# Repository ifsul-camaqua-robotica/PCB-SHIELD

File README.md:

# PCB-SHIELD
# Repositório para guardar o arquivo da PCB de um SHIELD para o carro da ROBOCUP 2025

- Arquivo "robocup-esp-32-1" -> Guarda os arquivos do KICAD para a PCB

- Arquivo "KICAD-LIBRARIES" -> Guarda as bibliotecas (footprints e symbols) utilizados para fazer a PCB
  (Não foi possível adicionar o arquivo da biblioteca utilizada "Espressif", porém no qual pode ser encontrada facilmente em repositório no github)

- Medindo do centro dos círculos até o centro deles.
- Cada um deles tem 3,5 mm das bordas (esta medida foi feita da borda dos círculos), e 3mm de diâmetro.
- Esquerda até Direita -> 84,5 mm
- Baixo até Cima -> 53mm

- Versão E-1.5

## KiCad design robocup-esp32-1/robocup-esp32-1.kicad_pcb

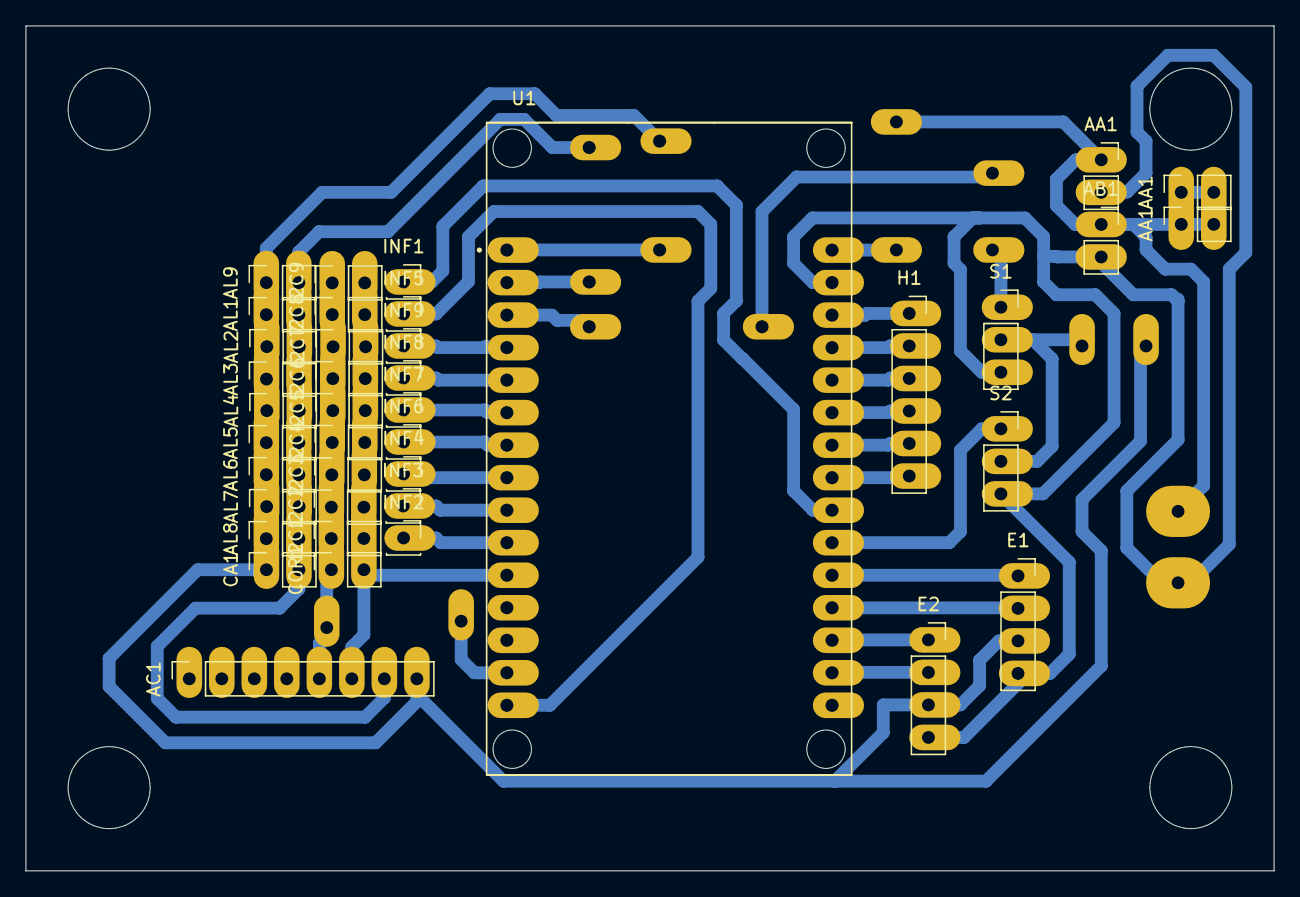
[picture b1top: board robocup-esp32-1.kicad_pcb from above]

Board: 2 copper layers, 97.5 x 66.0 mm, 40 parts (0 on the bottom side), 26 nets.

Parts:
AA1, AA1#2, AA1#3: VCCA, GNDA; PinSocket_1x02_P2.54mm_Vertical
AB1: VCCB, GNB; PinSocket_1x02_P2.54mm_Vertical
AC1: INT, ADD, XCL, XDA, SDA, SCL, GND, VCC; PinSocket_1x08_P2.54mm_Vertical
AL1, AL2, AL3, AL4, AL5, AL6, AL7, AL8, AL9: VCC, GND; PinSocket_1x02_P2.54mm_Vertical
CA1: VCC, GND; PinSocket_1x02_P2.54mm_Vertical
COR1: SDA, SCL; PinSocket_1x02_P2.54mm_Vertical
E1, E2: SA, SB, VCC, GND; PinSocket_1x04_P2.54mm_Vertical
H1: ENA, IN1, IN2, IN3, IN4, ENB; PinSocket_1x06_P2.54mm_Vertical
I2C1, I2C2, I2C3, I2C4, I2C5, I2C6, I2C7, I2C8, I2C9: SDA, SCL; PinSocket_1x02_P2.54mm_Vertical
INF1, INF2, INF3, INF4, INF5, INF6, INF7, INF8, INF9: XSHUT; PinSocket_1x01_P2.54mm_Vertical
S1, S2: SIGNAL, VCC, GND; PinSocket_1x03_P2.54mm_Vertical
U1: ESP32-DEVKIT-V1; MODULE_ESP32_DEVKIT_V1

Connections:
unnamed: AA1#3.1, AB1.1
unnamed: AA1#3.2, AB1.2, AC1.7, AL1.2, AL2.2, AL3.2, AL4.2, AL5.2, AL6.2, AL7.2, AL8.2, AL9.2, CA1.2, E1.4, E2.4, S1.3, S2.3, U1.2 (GND), U1.29 (GND)
unnamed: AC1.5, COR1.1, I2C1.1, I2C2.1, I2C3.1, I2C4.1, I2C5.1, I2C6.1, I2C7.1, I2C8.1, I2C9.1, U1.14 (D22)
unnamed: AC1.6, COR1.2, I2C1.2, I2C2.2, I2C3.2, I2C4.2, I2C5.2, I2C6.2, I2C7.2, I2C8.2, I2C9.2, U1.11 (D21)
unnamed: AC1.8, AL1.1, AL2.1, AL3.1, AL4.1, AL5.1, AL6.1, AL7.1, AL8.1, AL9.1, CA1.1, E1.3, E2.3, S1.2, S2.2, U1.1 (3V3)
unnamed: E1.1, U1.20 (D35)
unnamed: E1.2, U1.19 (D34)
unnamed: E2.1, U1.18 (VN)
unnamed: E2.2, U1.17 (VP)
unnamed: H1.1, U1.28 (D13)
unnamed: H1.2, U1.27 (D12)
unnamed: H1.3, U1.26 (D14)
unnamed: H1.4, U1.25 (D27)
unnamed: H1.5, U1.24 (D26)
unnamed: H1.6, U1.23 (D25)
unnamed: INF1.1, U1.22 (D33)
unnamed: INF2.1, U1.10 (D19)
unnamed: INF3.1, U1.9 (D18)
unnamed: INF4.1, U1.8 (D5)
unnamed: INF5.1, U1.15 (D23)
unnamed: INF6.1, U1.7 (TX2)
unnamed: INF7.1, U1.6 (RX2)
unnamed: INF8.1, U1.5 (D4)
unnamed: INF9.1, U1.4 (D2)
unnamed: S1.1, U1.3 (D15)
unnamed: S2.1, U1.21 (D32)

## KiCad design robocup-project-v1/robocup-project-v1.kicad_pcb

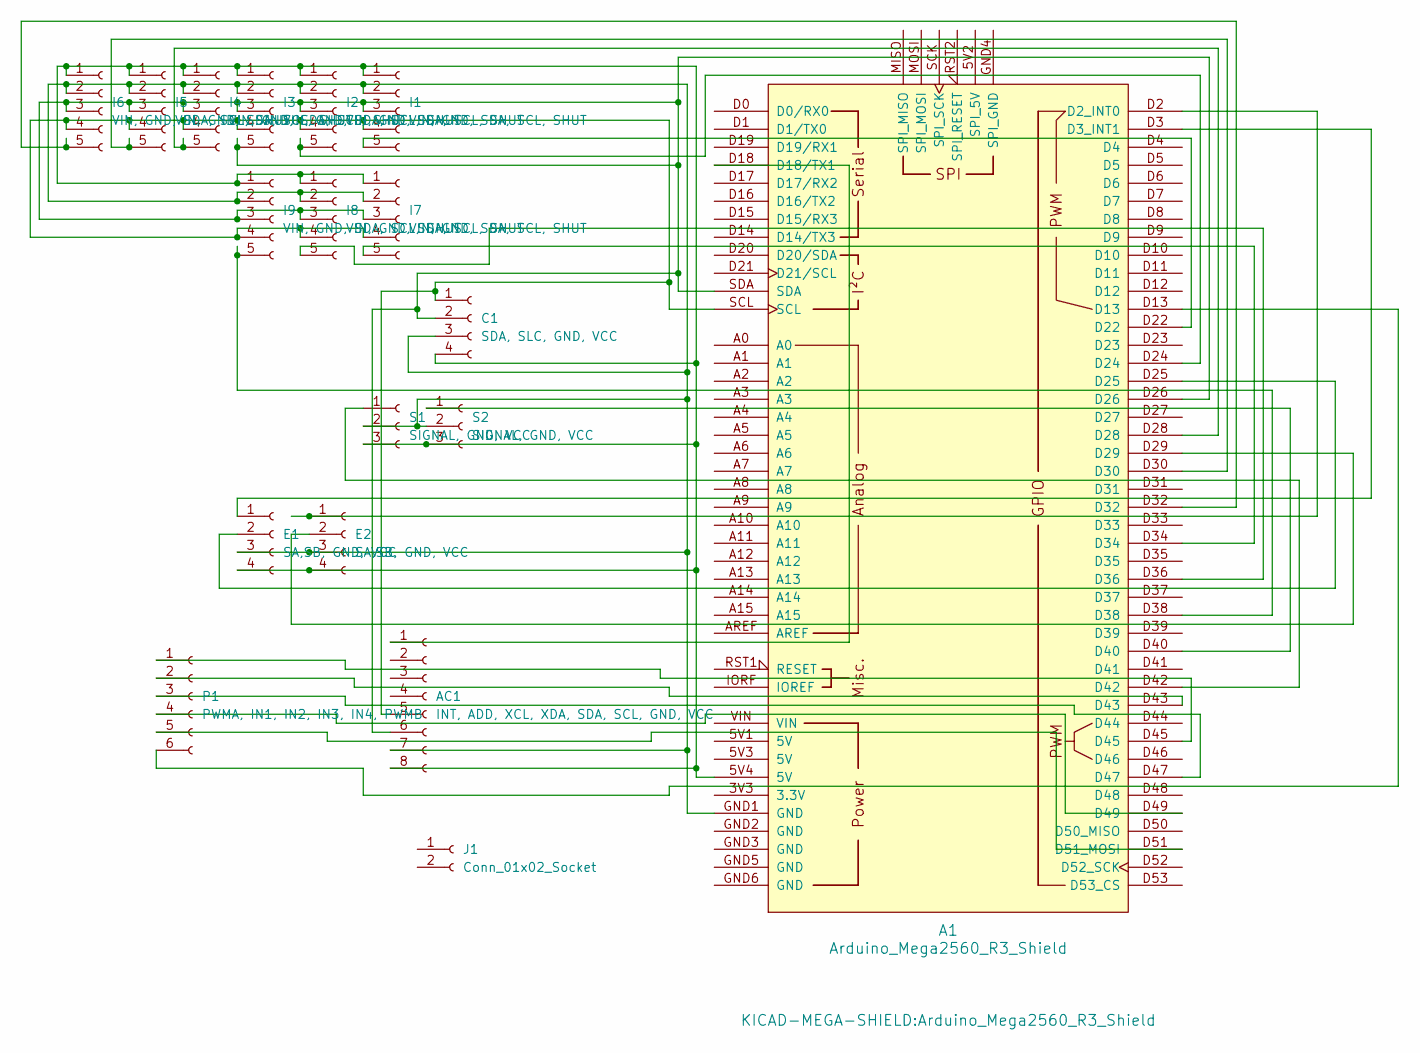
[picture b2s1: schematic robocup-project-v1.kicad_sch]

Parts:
A1: Arduino_Mega2560_R3_Shield
AC1: INT, ADD, XCL, XDA, SDA, SCL, GND, VCC; PinHeader_1x08_P2.54mm_Vertical
C1: SDA, SLC, GND, VCC; PinHeader_1x04_P2.54mm_Vertical
E1, E2: SA,SB, GND, VCC; PinHeader_1x04_P2.54mm_Vertical
I1, I2, I3, I4, I5, I6, I7, I8, I9: VIN, GND, SDA, SCL, SHUT; PinHeader_1x05_P2.54mm_Vertical
J1: Conn_01x02_Socket
P1: PWMA, IN1, IN2, IN3, IN4, PWMB; PinHeader_1x06_P2.54mm_Vertical
S1, S2: SIGNAL, GND, VCC; PinHeader_1x03_P2.54mm_Vertical

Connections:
unnamed: A1.D2 (D2_INT0), E2.1
unnamed: A1.D3 (D3_INT1), E1.1
unnamed: A1.D18 (D18/TX1), AC1.1
unnamed: A1.D51 (D51_MOSI), P1.5
unnamed: A1.SCL, AC1.5, C1.1, I1.4, I2.4, I3.4, I4.4, I5.4, I6.4, I7.4, I8.4, I9.4
unnamed: A1.D26, A1.SDA, AC1.6, C1.2, I1.3, I2.3, I3.3, I3.5, I4.3, I5.3, I6.3, I7.3, I8.3, I9.3
unnamed: A1.GND1 (GND), AC1.7, C1.3, E1.3, E2.3, I1.2, I2.2, I3.2, I4.2, I5.2, I6.2, I7.2, I8.2, I9.2, S1.2, S2.2
unnamed: A1.5V4 (5V), AC1.8, C1.4, E1.4, E2.4, I1.1, I2.1, I3.1, I4.1, I5.1, I6.1, I7.1, I8.1, I9.1, S1.3, S2.3
unnamed: A1.D25, E1.2
unnamed: A1.D29, E2.2
unnamed: A1.D22, I1.5
unnamed: A1.D24, I2.5
unnamed: A1.D28, I4.5
unnamed: A1.D30, I5.5
unnamed: A1.D32, I6.5
unnamed: A1.D34, I7.5
unnamed: A1.D36, I8.5
unnamed: A1.D38, I9.5
unnamed: A1.D45, P1.1
unnamed: A1.D43, P1.2
unnamed: A1.D47, P1.3
unnamed: A1.D49, P1.4
unnamed: A1.D13, P1.6
unnamed: A1.D42, S1.1
unnamed: A1.D40, S2.1

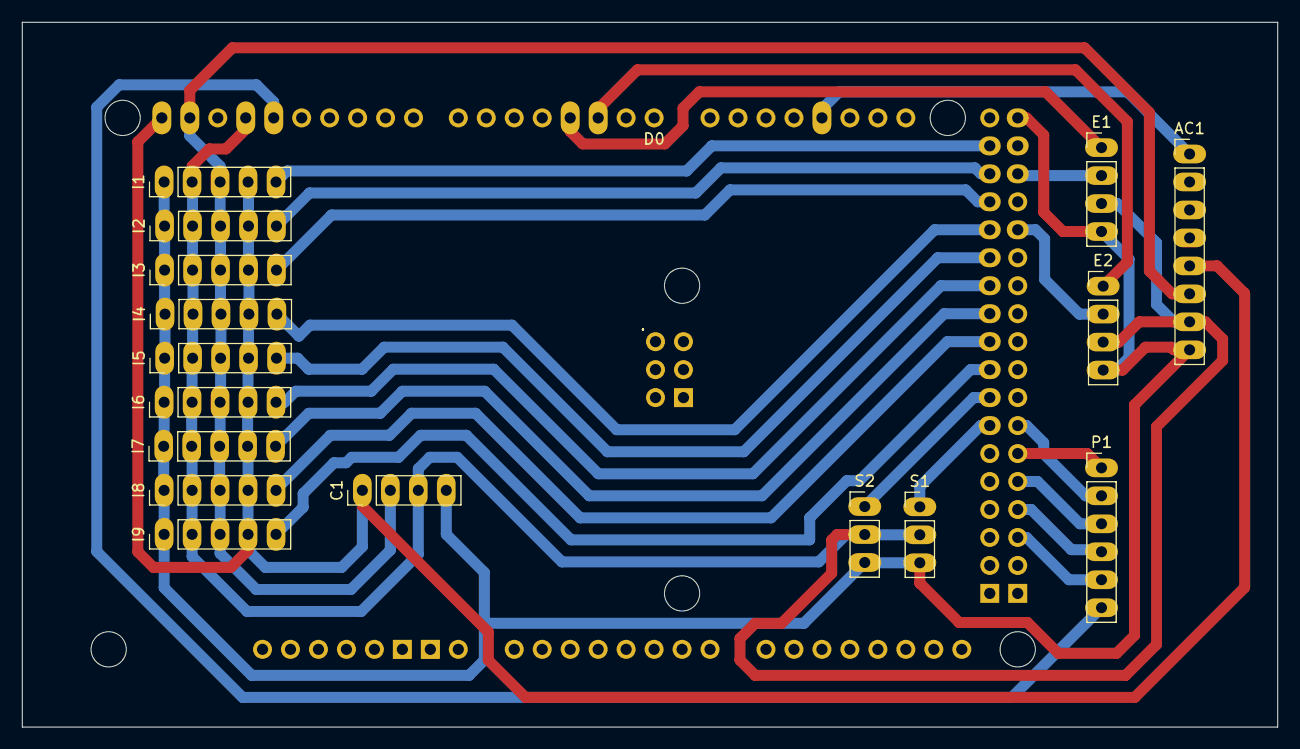
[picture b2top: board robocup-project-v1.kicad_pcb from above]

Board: 2 copper layers, 114.0 x 64.0 mm, 17 parts (0 on the bottom side), 25 nets.

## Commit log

2025-04-07 Arquivos da PCB para o SHIELD
    arquivos do KICAD para a PCB do SHIELD para o robo da ROBOCUP 2025
    Versão 1.0
2025-04-07 Arquivo do footprint utilizado
    Arquivo do footprint utilizado para o ARDUINO MEGA
2025-04-11 Mudamos toda a PCB
    trocamos o controlador para um esp-32, tivemos que mudar tudo.
2025-04-11 Adicionando Bibliotecas
    Adicionando arquivos das bibliotecas utilizadas para fazer a PCB para o ESP-32
    (não foi possivel adicionar a "Espressif"
2025-04-11 atualização da PCB
